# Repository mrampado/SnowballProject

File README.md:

# Snowball Project
The snowball project is named off the snowball method. It was started as an Arduino Learning Platform which was first designed as a simple way to teach my cousin Arduino in Nov 2021 without the frustration of breadboards, wiring, or polarity of LEDs. For many users wanting to start with Arduino, the hardware can be difficult to set up, troubleshoot, and is often not something that many want to deal with. This often leads to frustration in not knowing if the problem is software or hardware related, and the learning experience suffers. The goal of the project is to have an easy way for beginners to work with hardware

The snowball project was designed to maximize the setup of an Arduino, but in an all-in-one setup that requires no experience in hardware. Most importantly, it just works. 

## Initial Prototype

The initial prototype was designed over a weekend in November 2021, and subsequently manufactured by JLCPCB in time for me to deliver as Christmas gifts.  

/BoardPhotos/IMG_3308.JPEG)

### Hardware Overview

The initial prototype of the ALP system uses a mounted Arduino Nano onto a custom PCB, with all through hole components so it can easily be soldered by hand. The board had the following inputs and outputs
3 pushbuttons
3 rotational potentiometers
1 temperature sensor
1 light sensor
1 buzzer
6 5mm LEDs
10 WS2812b LEDs (similar to neopixels)
1 power LED

From this hardware, over 15 projects were ideated from the most basic of flashing an LED, to more complex utilizing the sensors to sound the buzzer or LEDs. All projects could be completed with the board, and only the board. This leads to ease of use in learning how to program Arduino without extra components to deal with. 

### Software Overview

A number of projects were developed as a way to test the board such as flashing the WS2812b LEDs:

https://user-images.githubusercontent.com/31992845/184553061-3517018b-8d40-42bd-8cc7-a411898c9277.MP4

Or a Star Wars theme [credit to original developer here](https://github.com/NassimBouyacoub/Star-Wars-theme-Song-Arduino-)

https://user-images.githubusercontent.com/31992845/184553076-f6d57d24-914b-4a0a-8b67-bb8ad6814c24.MP4

And many other projects that successfully allowed both myself, and those that I helped to learn Arduino to successfully start programming with little other work. Unfortunately, the software will not be released as it is being changed for the released version below that uses a new chip. 

However, for those that choose to build this initial prototype, the schematic can be used to reference pinout diagrams allowing you to use any other Arduino tutorial online to get started with programming. 

### Feedback on the Prototype

The feedback I received from both my cousin as well as others I gave the board to was awesome, however, with all projects there is always room for improvement. 

- The buttons are too small to easily press. As a manufacturing note, they also do not fit well into the board with glue being required at times to ensure real durability. 
- The rotational potentiometers are large, bulky, and easy to break off. 
- The temperature and light sensors are not attached to the board itself, and instead string off. This can lead to them being damaged in a backpack if not cared for properly.
- For my feedback, using an off the shelf component (specifically the Nano) at the time made sense, but long term is not practical as it adds both manufacturing complexity and reliance on other vendors. I plan to embed the Arduino into the board which will allow the prototyping lab (in my case JLCPCB) to fully assemble the test boards for me. Others can then also place an order for the same configuration without a need to source other components. 

## Released Version

The released version has not been fully designed, but is currently being worked on to mitigate many of the issues I have listed for the initial prototype. 

I am documenting the process in the format of the _Engineering Design Process_ and this will be released with the project, either here or on my website. The goal of this release is to not only provide the open source hardware, but also to explain the process of how to approach a problem, ideate potential solutions, and work towards developing a solution. 

As no software was released for the prototype project, I plan to release all code I have to work with the new board design as it fixes a few issues. The new hardware will use the ATMEGA32u4, which has built in USB. This will simplify the driver issues known around the legacy Arduinos (see FT232 known issues with Windows 11).

I expect this to be released by Christmas 2022.

## License

This hardware is covered under the CERN-OHL-S-V2 open source hardware license. Details on this license can also be found [at this link](https://choosealicense.com/licenses/cern-ohl-s-2.0/). 

Software for this project is covered under GNU Public License v3.0. Details on this license can be found [at this link](https://choosealicense.com/licenses/gpl-3.0/)

As per the details in each of the licenses, replication is accepted under the provision that all commercial and individual replications must also follow the same license as in this project, and **remain fully open source**. 

While not required, please contact me before starting any commercialization efforts. At the current moment, I am unable to commercialize this project thus unable to sell finished boards. I am happy to (in a limited capacity) support anyone / business that wants to utilize my efforts with ALP to use as a basis for teaching anyone and everyone Arduino. 

It is my personal belief that this project shall remain open source for the entire community, with all schematics, gerber files, and code available to all. I have benefited greatly from the open source community and this project will hopefully help others learn and get started too!

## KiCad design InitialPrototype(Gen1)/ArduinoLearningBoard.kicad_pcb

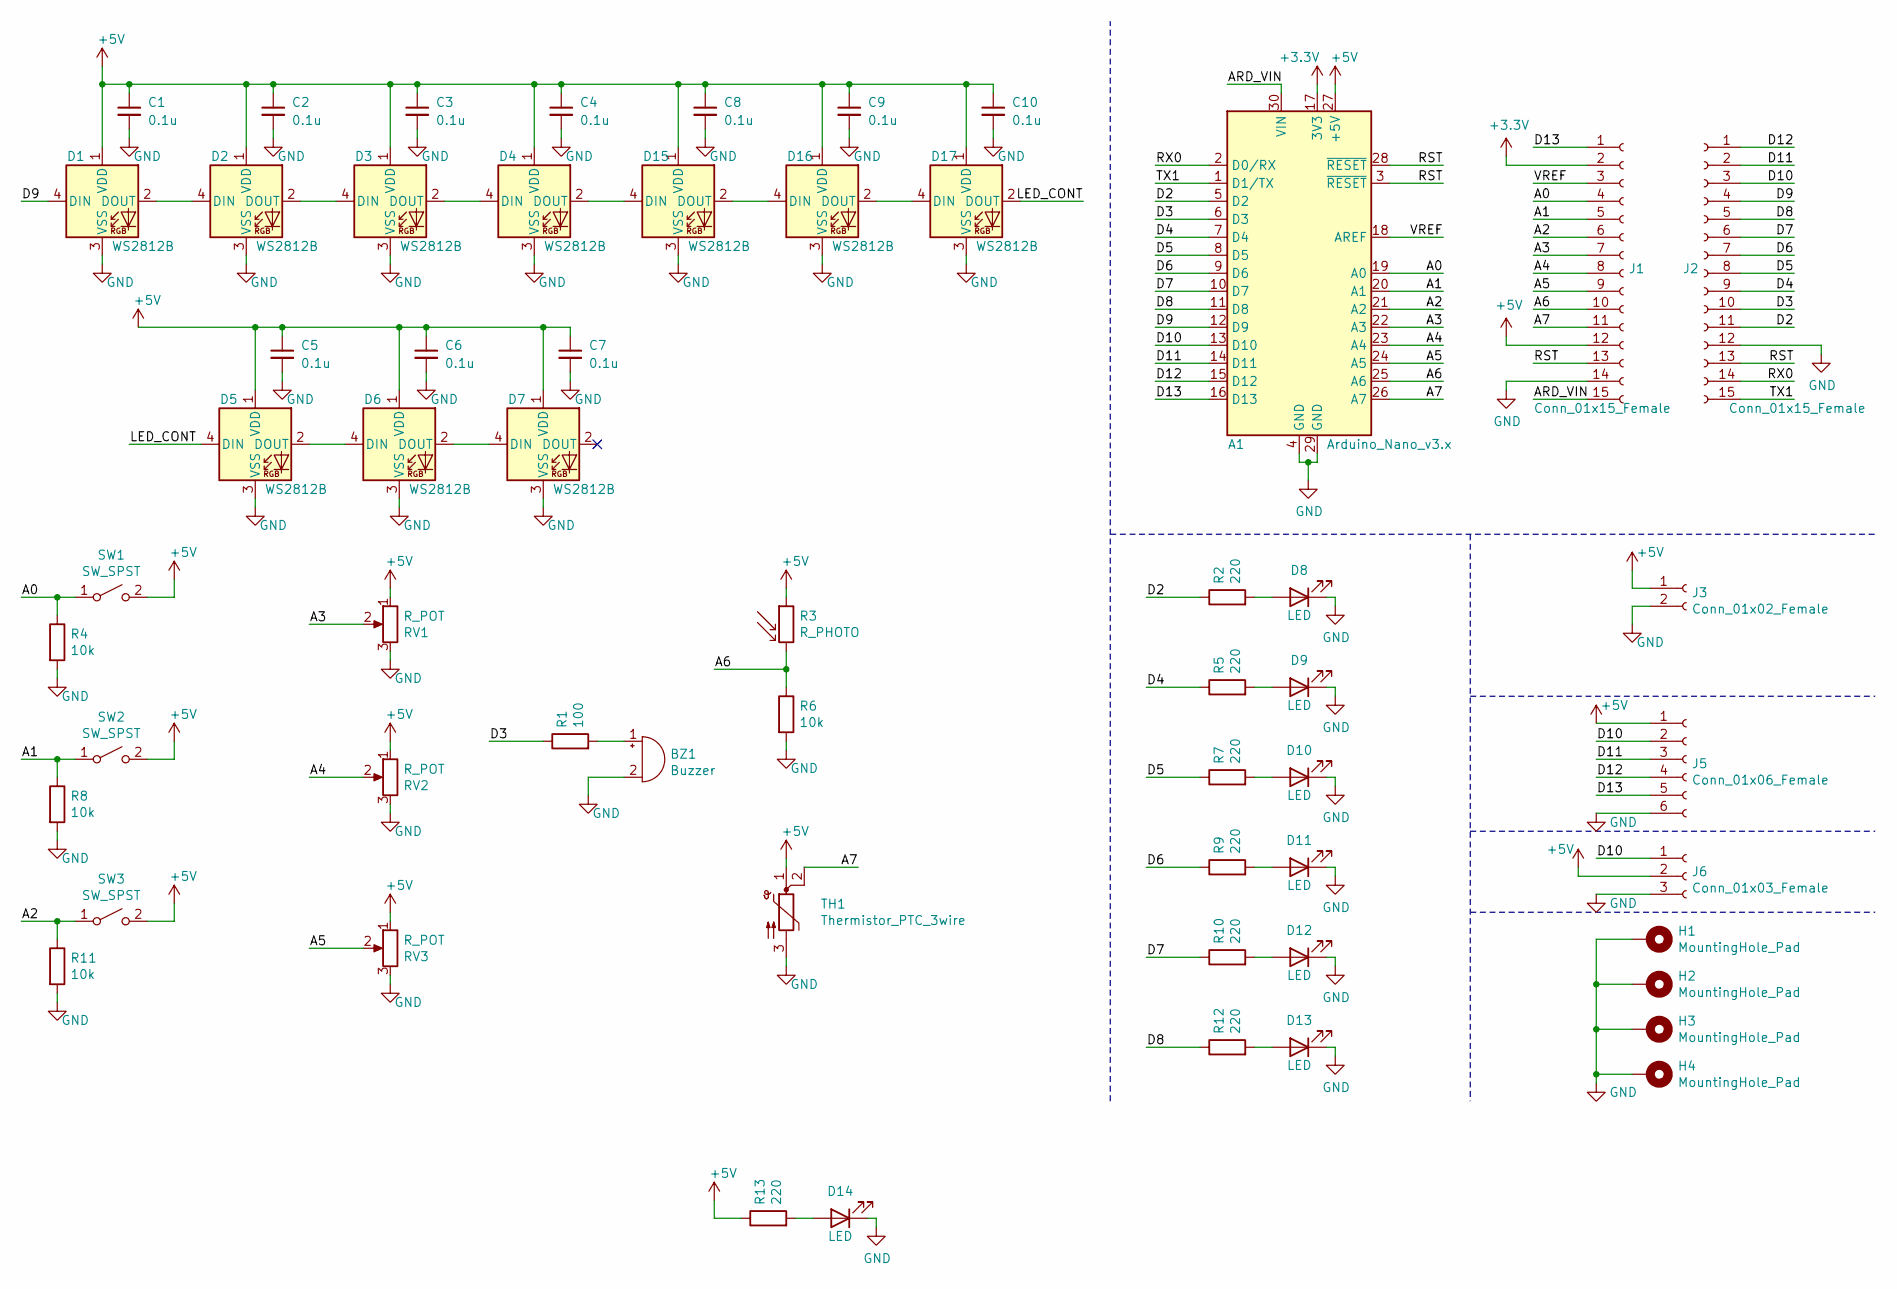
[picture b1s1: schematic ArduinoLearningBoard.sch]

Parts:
A1: Arduino_Nano_v3.x; Arduino_Nano
BZ1: Buzzer; Buzzer_TDK_PS1240P02BT_D12.2mm_H6.5mm; Digikey# 2104-TP124005-2CT-ND
C1, C2, C3, C4, C5, C6, C7, C8, C9, C10: 0.1u; C_0603_1608Metric_Pad1.05x0.95mm_HandSolder; Digikey# 478-10836-1-ND
D1, D2, D3, D4, D5, D6, D7, D15, D16, D17: WS2812B; LED_WS2812B_PLCC4_5.0x5.0mm_P3.2mm; Digikey# 1568-COM-16347CT-ND
D8, D14: LED; LED_D5.0mm_Clear; Digikey# 754-1732-ND
D9, D10, D11, D12, D13: LED; LED_D5.0mm_Clear
H1, H2, H3, H4: MountingHole_Pad; MountingHole_4.3mm_M4_Pad_Via
J1, J2: Conn_01x15_Female; PinHeader_1x15_P2.54mm_Vertical
J3: Conn_01x02_Female; PinHeader_1x02_P2.54mm_Vertical
J5: Conn_01x06_Female; PinHeader_1x06_P2.54mm_Vertical
J6: Conn_01x03_Female; PinHeader_1x03_P2.54mm_Vertical
R1: 100; R_Axial_DIN0207_L6.3mm_D2.5mm_P10.16mm_Horizontal
R2, R5, R7, R9, R10, R12, R13: 220; R_Axial_DIN0207_L6.3mm_D2.5mm_P10.16mm_Horizontal
R3: R_PHOTO; R_Axial_DIN0207_L6.3mm_D2.5mm_P10.16mm_Horizontal
R4, R6, R8, R11: 10k; R_Axial_DIN0207_L6.3mm_D2.5mm_P10.16mm_Horizontal
RV1, RV2, RV3: R_POT; Potentiometer_Bourns_PTV09A-1_Single_Vertical; Digikey# PTV09A-4220F-B103-ND
SW1, SW2, SW3: SW_SPST; SW_DIP_SPSTx01_Slide_6.7x4.1mm_W7.62mm_P2.54mm_LowProfile; Digikey# CKN12306-ND
TH1: Thermistor_PTC_3wire; TO-126-3_Vertical; Digikey# TMP36GT9Z-ND

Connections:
+3V3: A1.17 (3V3), J1.2
+5V: A1.27 (+5V), C1.1, C2.1, C3.1, C4.1, C5.1, C6.1, C7.1, C8.1, C9.1, C10.1, D1.1 (VDD), D2.1 (VDD), D3.1 (VDD), D4.1 (VDD), D5.1 (VDD), D6.1 (VDD), D7.1 (VDD), D15.1 (VDD), D16.1 (VDD), D17.1 (VDD), J1.12, J3.1, J5.1, J6.2, R3.1, R13.1, RV1.1, RV2.1, RV3.1, SW1.2 (B), SW2.2 (B), SW3.2 (B), TH1.1
/A0: A1.19 (A0), J1.4, R4.1, SW1.1 (A)
/A1: A1.20 (A1), J1.5, R8.1, SW2.1 (A)
/A2: A1.21 (A2), J1.6, R11.1, SW3.1 (A)
/A3: A1.22 (A3), J1.7, RV1.2
/A4: A1.23 (A4), J1.8, RV2.2
/A5: A1.24 (A5), J1.9, RV3.2
/A6: A1.25 (A6), J1.10, R3.2, R6.1
/A7: A1.26 (A7), J1.11, TH1.2
/ARD_VIN: A1.30 (VIN), J1.15
/D2: A1.5 (D2), J2.11, R2.1
/D3: A1.6 (D3), J2.10, R1.1
/D4: A1.7 (D4), J2.9, R5.1
/D5: A1.8 (D5), J2.8, R7.1
/D6: A1.9 (D6), J2.7, R9.1
/D7: A1.10 (D7), J2.6, R10.1
/D8: A1.11 (D8), J2.5, R12.1
/D9: A1.12 (D9), D1.4 (DIN), J2.4
/D10: A1.13 (D10), J2.3, J5.2, J6.1
/D11: A1.14 (D11), J2.2, J5.3
/D12: A1.15 (D12), J2.1, J5.4
/D13: A1.16 (D13), J1.1, J5.5
/LED_CONT: D5.4 (DIN), D17.2 (DOUT)
/RST: A1.3 (~RESET), A1.28 (~RESET), J1.13, J2.13
/RX0: A1.2 (D0/RX), J2.14
/TX1: A1.1 (D1/TX), J2.15
/VREF: A1.18 (AREF), J1.3
GND: A1.4 (GND), A1.29 (GND), BZ1.2 (+), C1.2, C2.2, C3.2, C4.2, C5.2, C6.2, C7.2, C8.2, C9.2, C10.2, D1.3 (VSS), D2.3 (VSS), D3.3 (VSS), D4.3 (VSS), D5.3 (VSS), D6.3 (VSS), D7.3 (VSS), D8.1 (K), D9.1 (K), D10.1 (K), D11.1 (K), D12.1 (K), D13.1 (K), D14.1 (K), D15.3 (VSS), D16.3 (VSS), D17.3 (VSS), H1.1, H2.1, H3.1, H4.1, J1.14, J2.12, J3.2, J5.6, J6.3, R4.2, R6.2, R8.2, R11.2, RV1.3, RV2.3, RV3.3, TH1.3
unnamed: BZ1.1 (-), R1.2
unnamed: D1.2 (DOUT), D2.4 (DIN)
unnamed: D2.2 (DOUT), D3.4 (DIN)
unnamed: D3.2 (DOUT), D4.4 (DIN)
unnamed: D5.2 (DOUT), D6.4 (DIN)
unnamed: D6.2 (DOUT), D7.4 (DIN)
unnamed: D8.2 (A), R2.2
unnamed: D9.2 (A), R5.2
unnamed: D10.2 (A), R7.2
unnamed: D11.2 (A), R9.2
unnamed: D12.2 (A), R10.2
unnamed: D13.2 (A), R12.2
unnamed: D14.2 (A), R13.2
unnamed: D15.2 (DOUT), D16.4 (DIN)
unnamed: D4.2 (DOUT), D15.4 (DIN)
unnamed: D16.2 (DOUT), D17.4 (DIN)

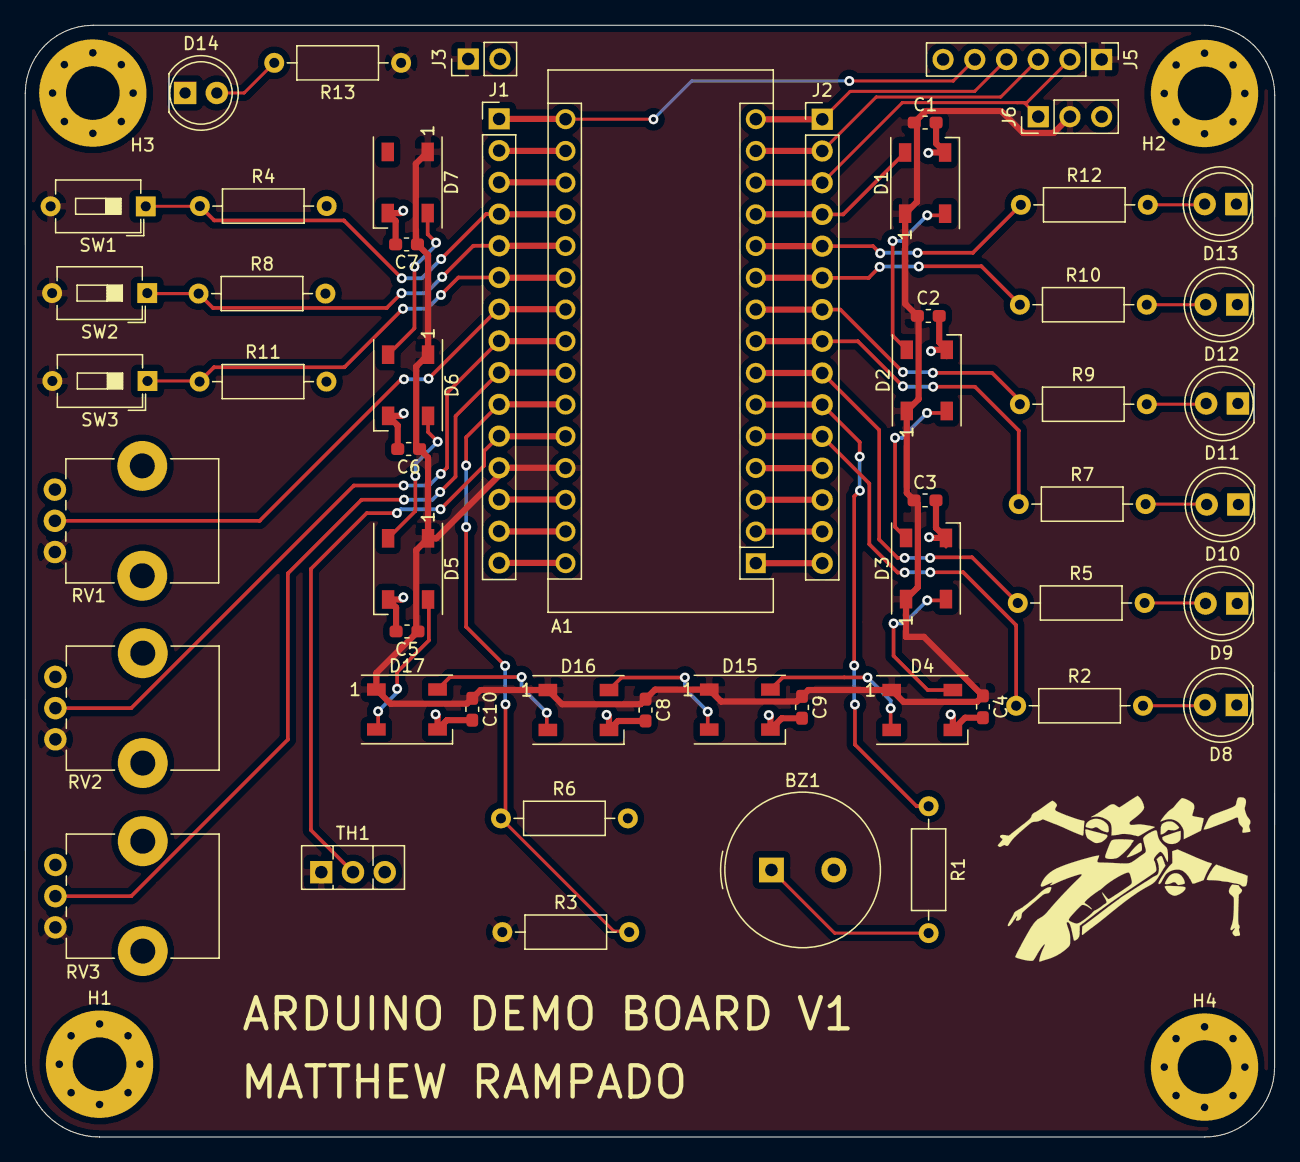
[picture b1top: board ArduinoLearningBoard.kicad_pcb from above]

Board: 2 copper layers, 100.1 x 89.0 mm, 58 parts (0 on the bottom side), 45 nets.

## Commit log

2022-08-14 Added CERN Open Source License
2022-08-14 Adding local git repository dated from Nov 2021
    Publishing my local git repository to github for sharing as I continue to develop this project
2022-08-14 Updated README with the work from the Prototype
2022-08-14 Added GNU License for software
2022-08-15 Created KiCad v6 Project
2022-08-15 Added CERN note in schematic
2022-08-15 ATMEGA32U4 selected
    Power circuitry completed
    Analog power circuitry completed
    External crystal circuitry completed
2022-08-15 Fixed bullet points not working
2022-08-15 Arduino micro pinouts added
2022-08-24 Added USBC and ISP Programming Header
2022-08-24 Added LEDs, footprints, and part#s to schematic
2022-08-24 Power Protection Added
2022-08-24 Base Schematic Done before peripherals added
2022-08-26 Base Schematic Minor Edits
2023-06-10 Removed blank files
2023-06-10 Added Side LEDs to go on bottom
2023-06-11 Project rename
2023-06-11 Removed old files
2023-06-11 Removed backups from git
2023-06-11 Removed kicad backup files
2023-06-11 Updated gitignore
2023-06-11 Work for night
2023-10-02 Added other input devices based on hardware spec sheet
2023-10-02 Added addressable LEDs
2023-10-02 Added in cool buttons
